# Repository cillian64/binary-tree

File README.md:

# binary-tree
A simple electronic christmas tree ornament, intended for teaching electronics.

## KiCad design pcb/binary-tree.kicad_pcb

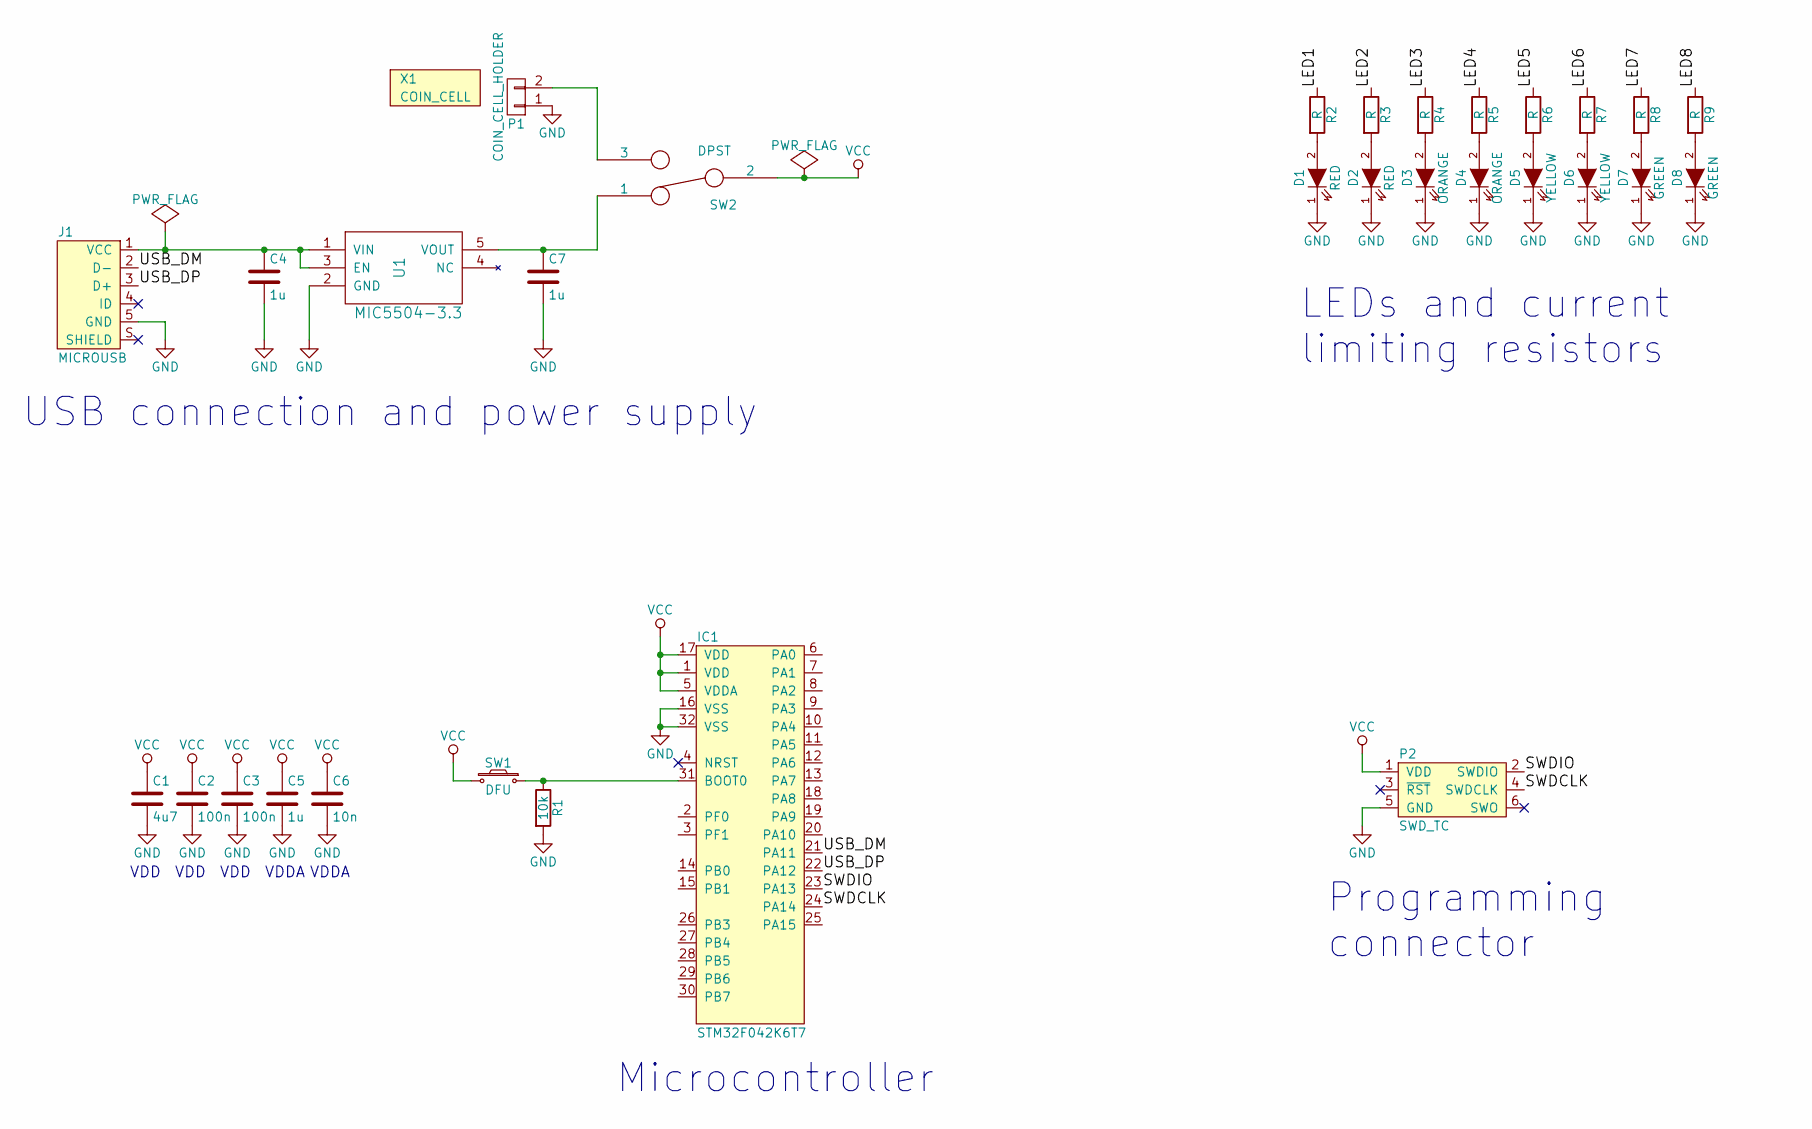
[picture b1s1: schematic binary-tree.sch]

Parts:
C1: 4u7; 0805; Farnell 1759420
C2, C3: 100n; 0805; Farnell 1759265
C4, C5, C7: 1u; 0805; Farnell 2320853
C6: 10n; 0805; Farnell 1759246
D1, D2: RED; 0805-LED; Farnell 2099241
D3, D4: ORANGE; 0805-LED; Farnell 2099237
D5, D6: YELLOW; 0805-LED; Farnell 2099242
D7, D8: GREEN; 0805-LED; Farnell 2099235
IC1: STM32F042K6T7; LQFP-32; Farnell 2469553
J1: MICROUSB; MICROUSB_MOLEX_47589-0001; Farnell 1568023
P1: COIN_CELL_HOLDER; Farnell 2064715
P2: SWD_TC; TC2030-NL
R1: 10k; 0805; Farnell 9332391
R2, R3, R4, R5, R6, R7, R8, R9: R; 0805
SW1: DFU; KSEMxxJLFS; Farnell 2435311
SW2: DPST; OS102011MS2QN1; Farnell 1201430
U1: MIC5504-3.3; SOT-23-5; Farnell 2510377
X1: COIN_CELL; Farnell 2065171

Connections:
/LED1: IC1.6 (PA0), R2.1
/LED2: IC1.7 (PA1), R3.1
/LED3: IC1.8 (PA2), R4.1
/LED4: IC1.9 (PA3), R5.1
/LED5: IC1.10 (PA4), R6.1
/LED6: IC1.12 (PA6), R7.1
/LED7: IC1.13 (PA7), R8.1
/LED8: IC1.14 (PB0), R9.1
/SWDCLK: IC1.24 (PA14), P2.4 (SWDCLK)
/SWDIO: IC1.23 (PA13), P2.2 (SWDIO)
/USB_DM: IC1.21 (PA11), J1.2 (D-)
/USB_DP: IC1.22 (PA12), J1.3 (D+)
GND: C1.2, C2.2, C3.2, C4.2, C5.2, C6.2, C7.2, D1.1 (K), D2.1 (K), D3.1 (K), D4.1 (K), D5.1 (K), D6.1 (K), D7.1 (K), D8.1 (K), IC1.16 (VSS), IC1.32 (VSS), J1.5 (GND), P1.1, P2.5 (GND), R1.2, U1.2 (GND)
unnamed: C4.1, J1.1 (VCC), U1.1 (VIN), U1.3 (EN)
unnamed: C7.1, SW2.1, U1.5 (VOUT)
unnamed: D1.2 (A), R2.2
unnamed: D2.2 (A), R3.2
unnamed: D3.2 (A), R4.2
unnamed: D4.2 (A), R5.2
unnamed: D5.2 (A), R6.2
unnamed: D6.2 (A), R7.2
unnamed: D7.2 (A), R8.2
unnamed: D8.2 (A), R9.2
unnamed: IC1.31 (BOOT0), R1.1, SW1.2
unnamed: P1.2, SW2.3
VCC: C1.1, C2.1, C3.1, C5.1, C6.1, IC1.1 (VDD), IC1.5 (VDDA), IC1.17 (VDD), P2.1 (VDD), SW1.1, SW2.2

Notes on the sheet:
USB connection and power supply
Microcontroller
LEDs and current limiting resistors
Programming connector
VDD
VDDA

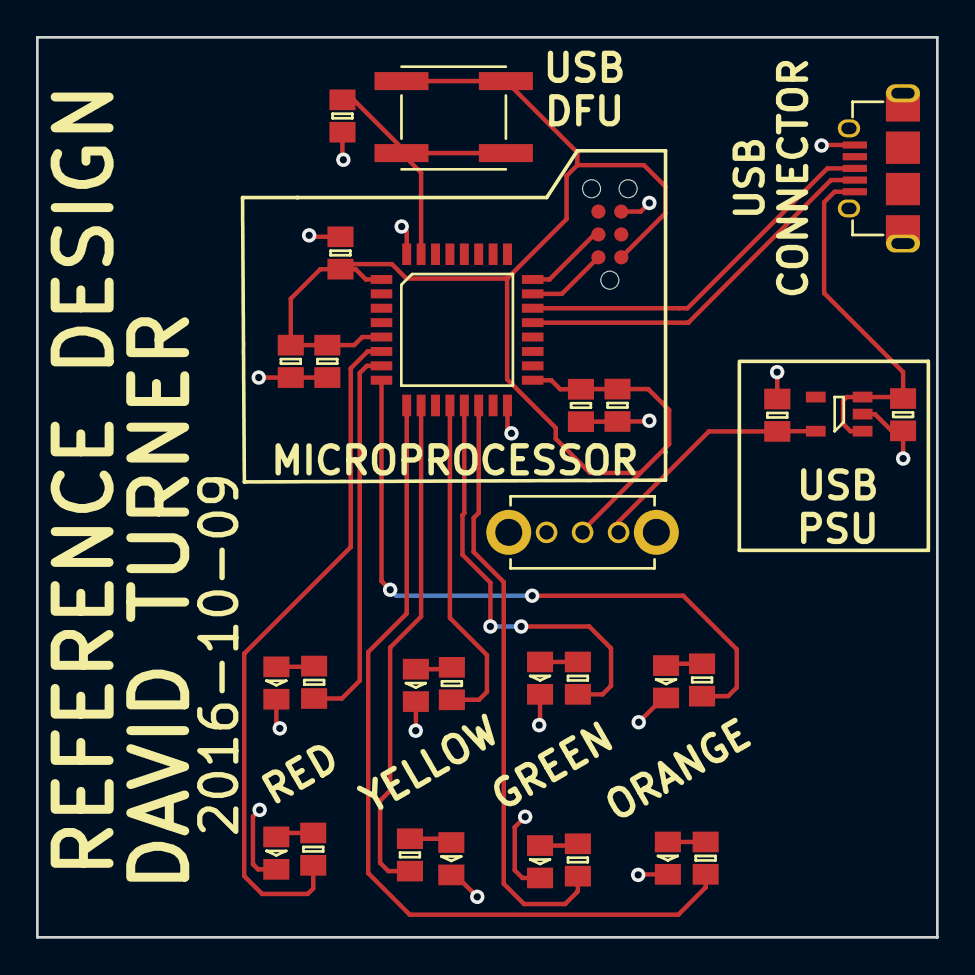
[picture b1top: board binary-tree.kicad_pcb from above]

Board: 2 copper layers, 50.0 x 50.0 mm, 30 parts (0 on the bottom side), 25 nets.

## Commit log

2016-10-09 Schematic and placement minus coin cell
2016-10-09 Routed reference board
